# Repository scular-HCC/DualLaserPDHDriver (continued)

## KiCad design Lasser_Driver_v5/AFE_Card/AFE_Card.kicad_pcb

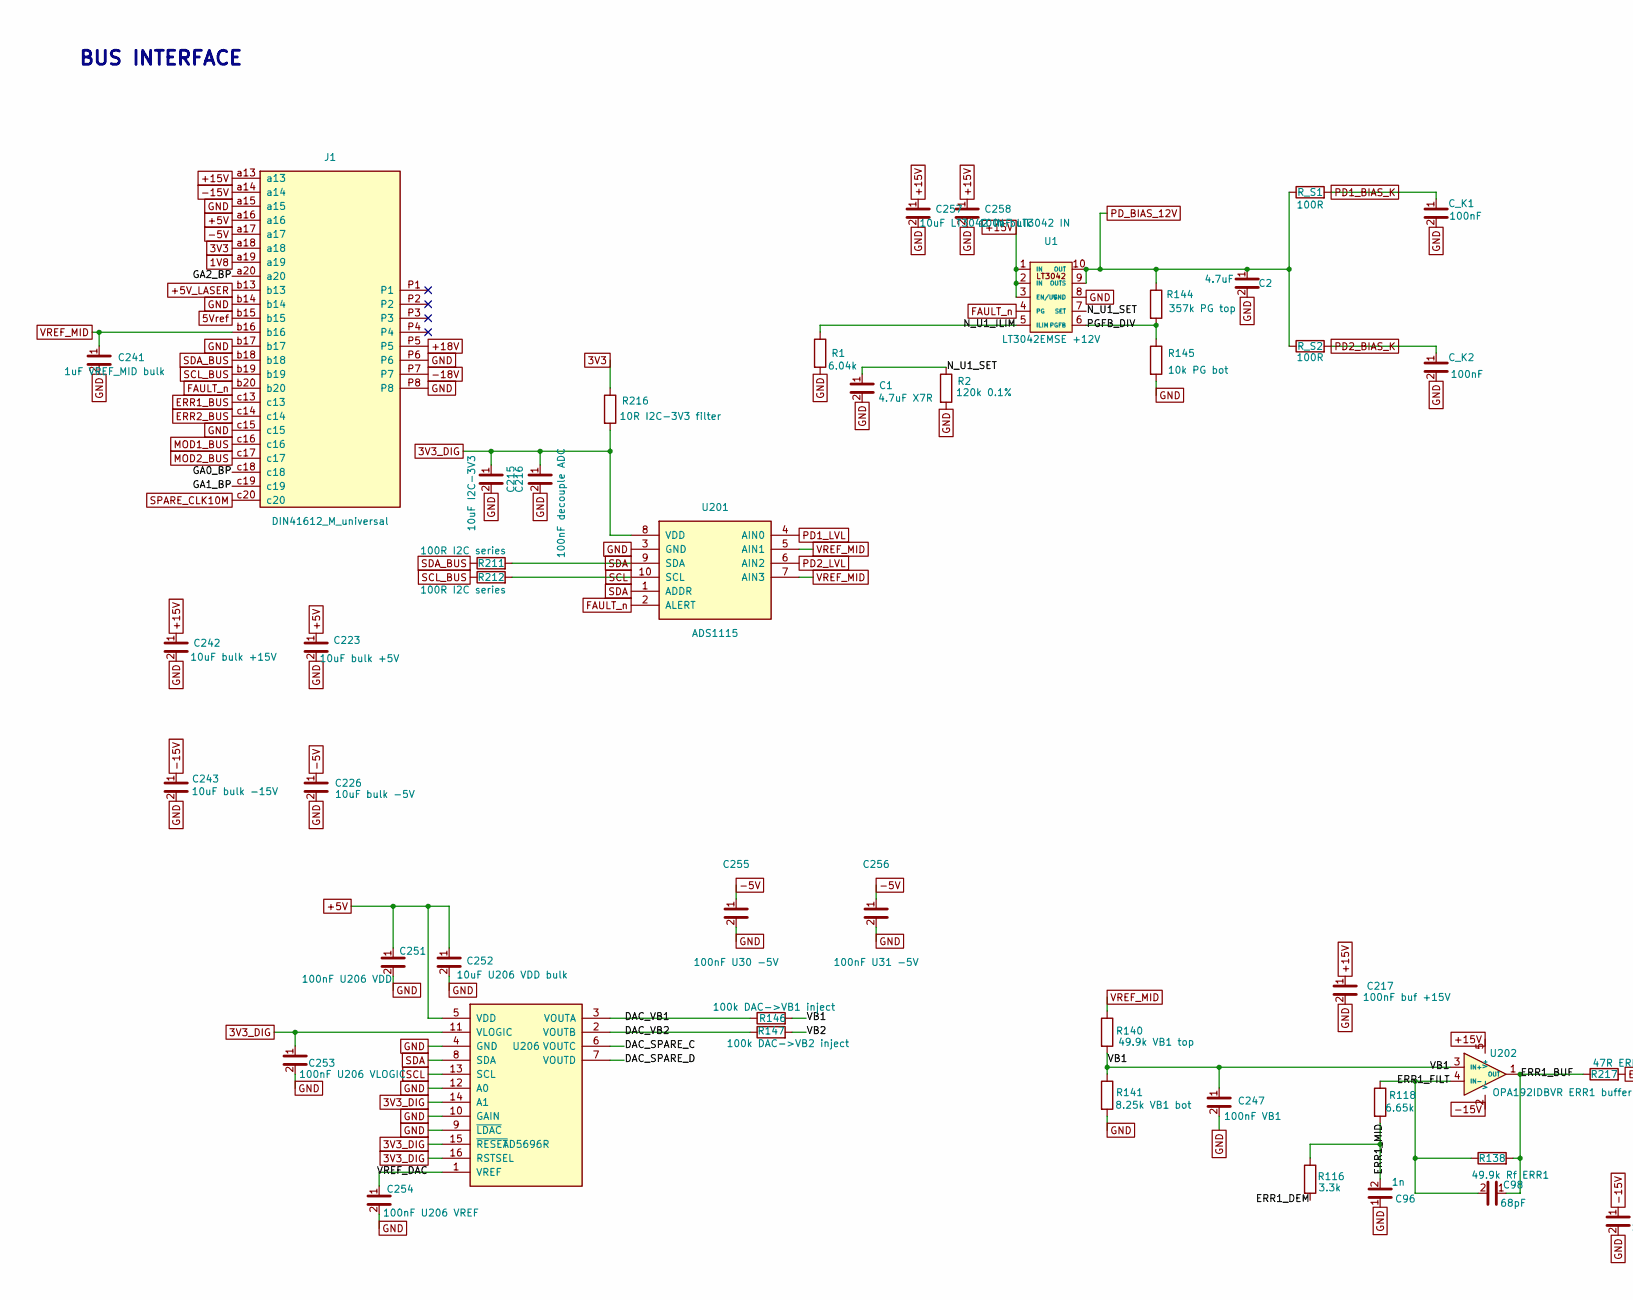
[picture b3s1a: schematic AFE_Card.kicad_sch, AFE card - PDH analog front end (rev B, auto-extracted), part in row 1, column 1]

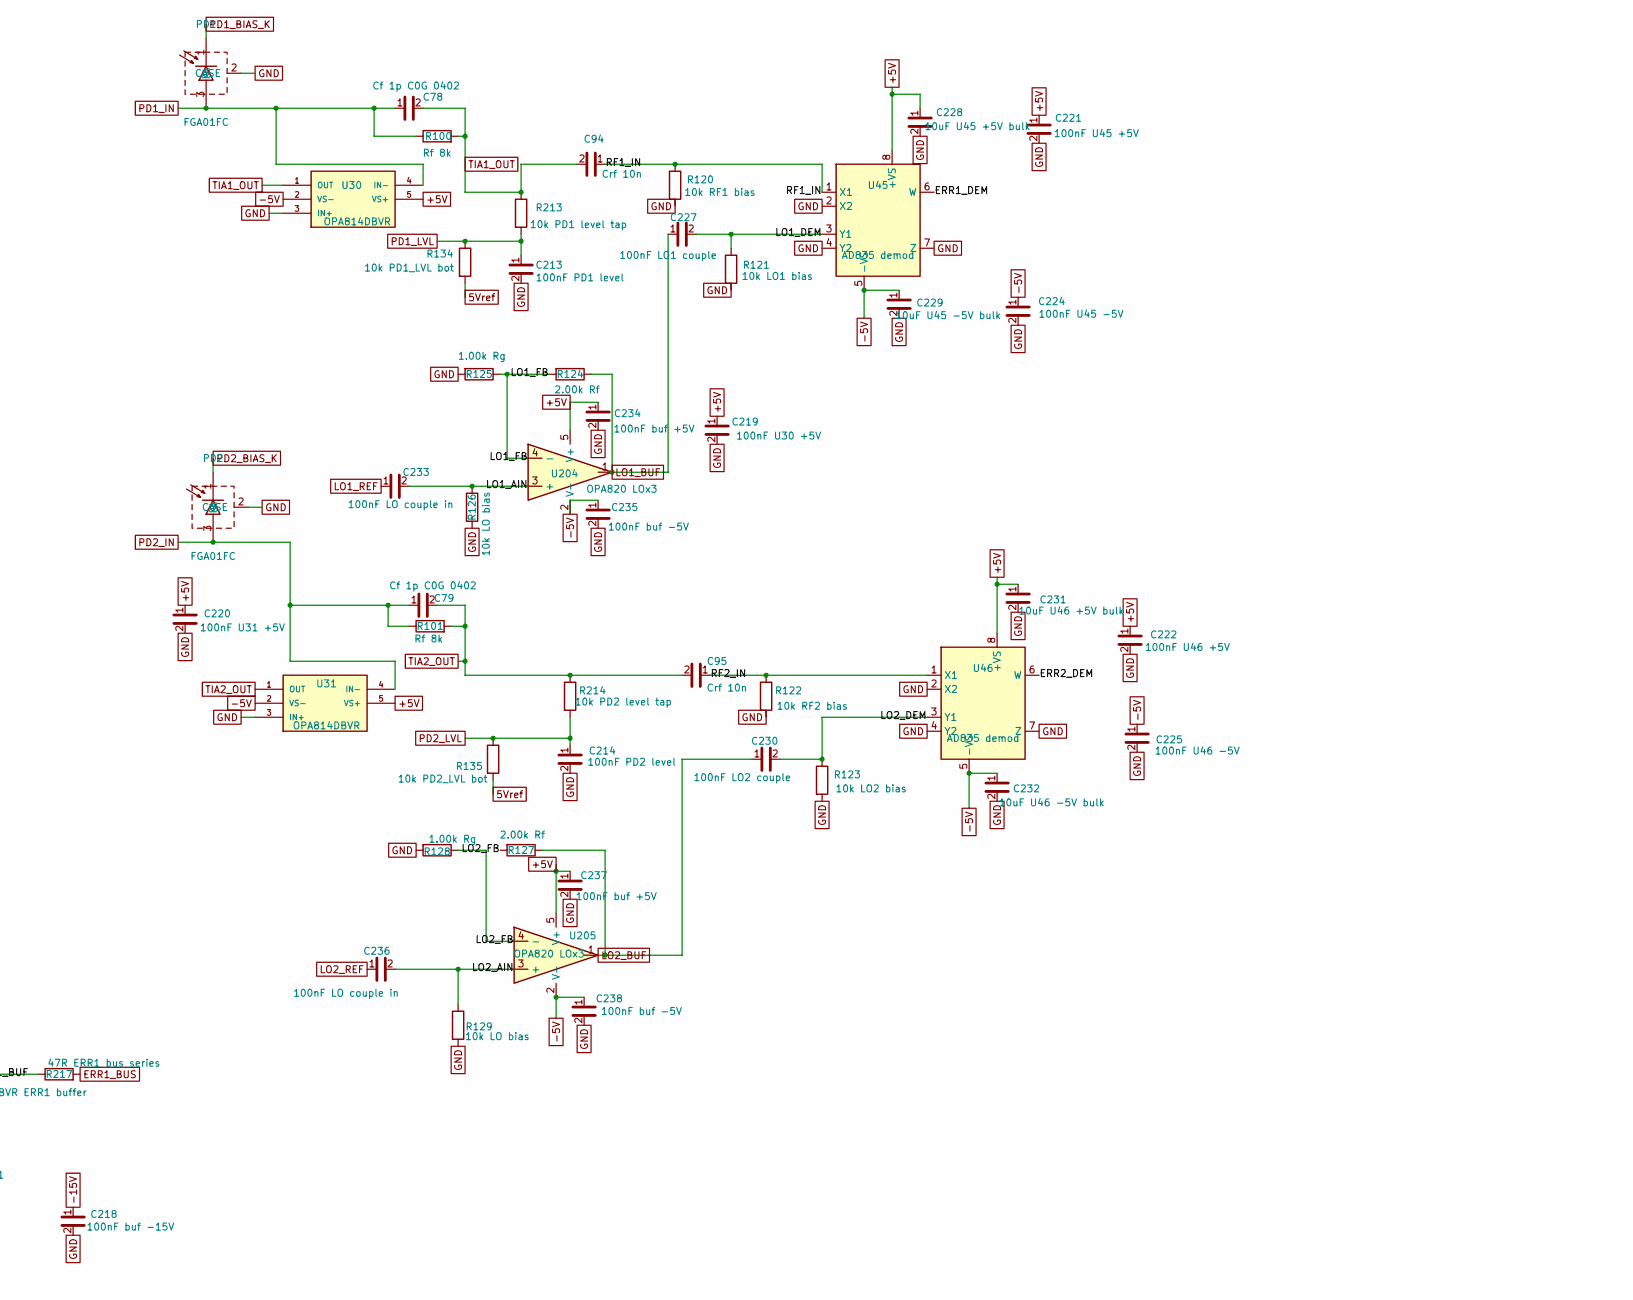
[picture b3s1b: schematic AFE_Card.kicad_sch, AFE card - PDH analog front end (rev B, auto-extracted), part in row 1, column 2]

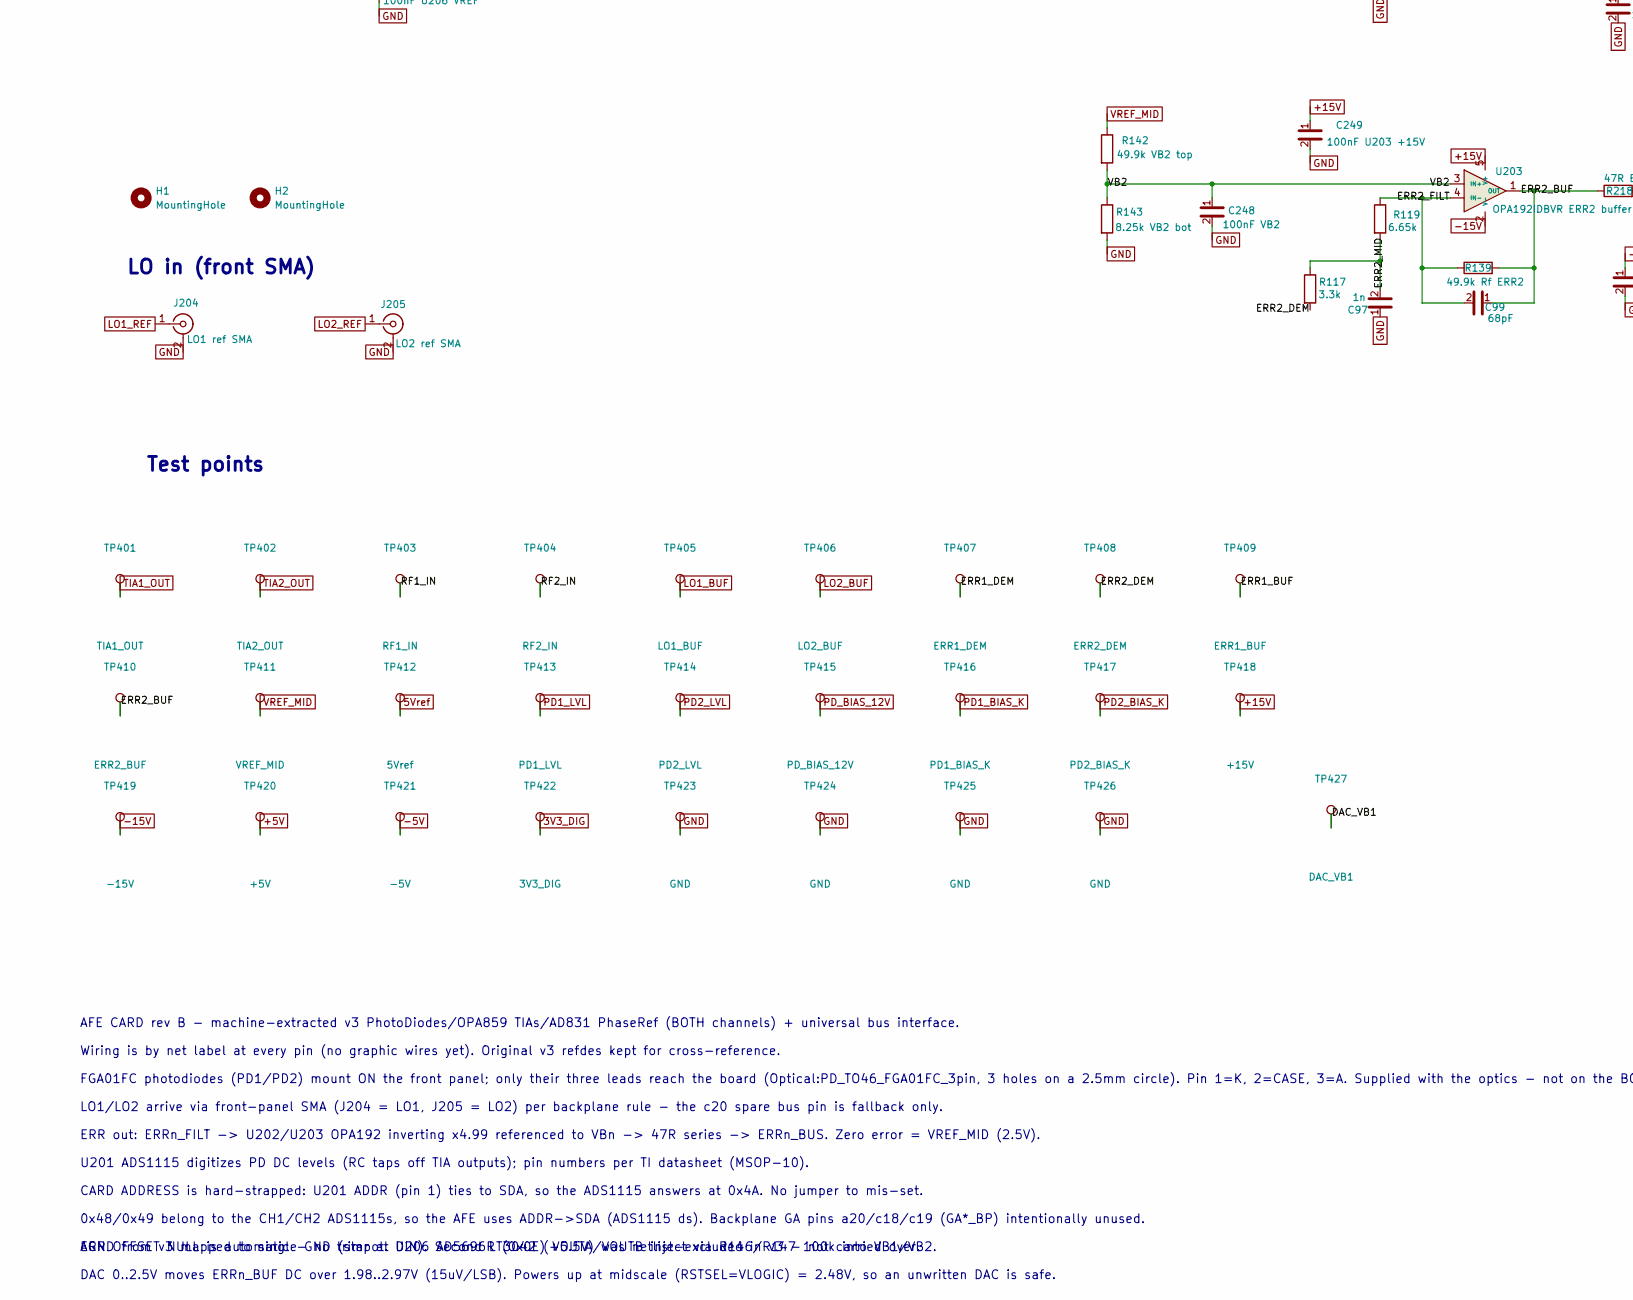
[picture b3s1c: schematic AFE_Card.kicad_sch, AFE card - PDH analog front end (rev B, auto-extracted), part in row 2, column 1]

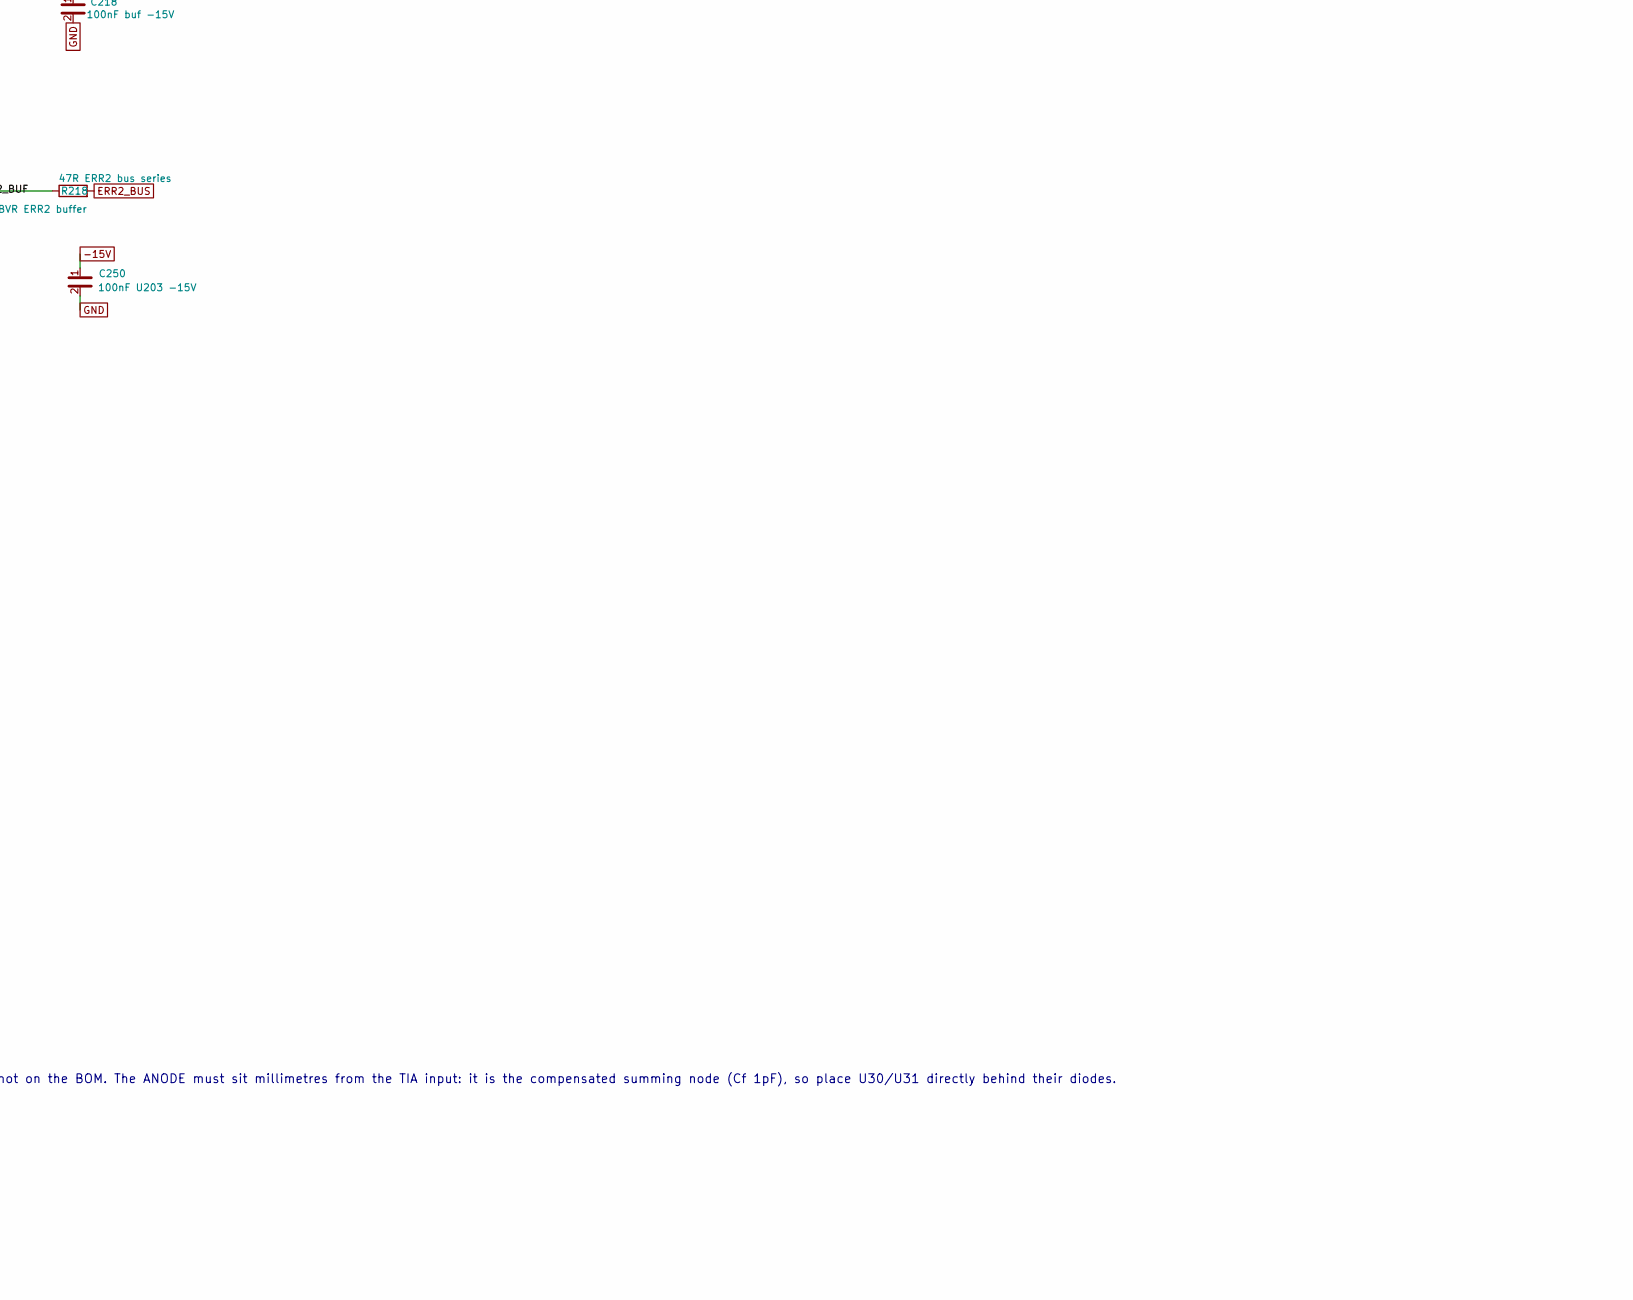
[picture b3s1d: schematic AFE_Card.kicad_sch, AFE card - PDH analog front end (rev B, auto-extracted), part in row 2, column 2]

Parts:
C1: 4.7uF X7R; C_0805_2012Metric_Pad1.18x1.45mm_HandSolder
C2: 4.7uF; C_0805_2012Metric_Pad1.18x1.45mm_HandSolder
C78, C79: Cf 1p C0G 0402; C_0402_1005Metric_Pad0.74x0.62mm_HandSolder
C94, C95: Crf 10n; C_0805_2012Metric_Pad1.18x1.45mm_HandSolder
C96, C97: 1n; C_0805_2012Metric_Pad1.18x1.45mm_HandSolder
C98, C99: 68pF; C_0805_2012Metric_Pad1.18x1.45mm_HandSolder
C213: 100nF PD1 level; C_0805_2012Metric_Pad1.18x1.45mm_HandSolder
C214: 100nF PD2 level; C_0805_2012Metric_Pad1.18x1.45mm_HandSolder
C215: 10uF I2C-3V3; C_0805_2012Metric_Pad1.18x1.45mm_HandSolder
C216: 100nF decouple ADC; C_0805_2012Metric_Pad1.18x1.45mm_HandSolder
C217: 100nF buf +15V; C_0805_2012Metric_Pad1.18x1.45mm_HandSolder
C218: 100nF buf -15V; C_0805_2012Metric_Pad1.18x1.45mm_HandSolder
C219: 100nF U30 +5V; C_0805_2012Metric_Pad1.18x1.45mm_HandSolder
C220: 100nF U31 +5V; C_0805_2012Metric_Pad1.18x1.45mm_HandSolder
C221: 100nF U45 +5V; C_0805_2012Metric_Pad1.18x1.45mm_HandSolder
C222: 100nF U46 +5V; C_0805_2012Metric_Pad1.18x1.45mm_HandSolder
C223: 10uF bulk +5V; C_0805_2012Metric_Pad1.18x1.45mm_HandSolder
C224: 100nF U45 -5V; C_0805_2012Metric_Pad1.18x1.45mm_HandSolder
C225: 100nF U46 -5V; C_0805_2012Metric_Pad1.18x1.45mm_HandSolder
C226: 10uF bulk -5V; C_0805_2012Metric_Pad1.18x1.45mm_HandSolder
C227: 100nF LO1 couple; C_0805_2012Metric_Pad1.18x1.45mm_HandSolder
C228: 10uF U45 +5V bulk; C_0805_2012Metric_Pad1.18x1.45mm_HandSolder
C229: 10uF U45 -5V bulk; C_0805_2012Metric_Pad1.18x1.45mm_HandSolder
C230: 100nF LO2 couple; C_0805_2012Metric_Pad1.18x1.45mm_HandSolder
C231: 10uF U46 +5V bulk; C_0805_2012Metric_Pad1.18x1.45mm_HandSolder
C232: 10uF U46 -5V bulk; C_0805_2012Metric_Pad1.18x1.45mm_HandSolder
C233, C236: 100nF LO couple in; C_0805_2012Metric_Pad1.18x1.45mm_HandSolder
C234, C237: 100nF buf +5V; C_0805_2012Metric_Pad1.18x1.45mm_HandSolder
C235, C238: 100nF buf -5V; C_0805_2012Metric_Pad1.18x1.45mm_HandSolder
C241: 1uF VREF_MID bulk; C_0805_2012Metric_Pad1.18x1.45mm_HandSolder
C242: 10uF bulk +15V; C_0805_2012Metric_Pad1.18x1.45mm_HandSolder
C243: 10uF bulk -15V; C_0805_2012Metric_Pad1.18x1.45mm_HandSolder
C247: 100nF VB1; C_0805_2012Metric_Pad1.18x1.45mm_HandSolder
C248: 100nF VB2; C_0805_2012Metric_Pad1.18x1.45mm_HandSolder
C249: 100nF U203 +15V; C_0805_2012Metric_Pad1.18x1.45mm_HandSolder
C250: 100nF U203 -15V; C_0805_2012Metric_Pad1.18x1.45mm_HandSolder
C251: 100nF U206 VDD; C_0805_2012Metric_Pad1.18x1.45mm_HandSolder
C252: 10uF U206 VDD bulk; C_0805_2012Metric_Pad1.18x1.45mm_HandSolder
C253: 100nF U206 VLOGIC; C_0805_2012Metric_Pad1.18x1.45mm_HandSolder
C254: 100nF U206 VREF; C_0805_2012Metric_Pad1.18x1.45mm_HandSolder
C255: 100nF U30 -5V; C_0805_2012Metric_Pad1.18x1.45mm_HandSolder
C256: 100nF U31 -5V; C_0805_2012Metric_Pad1.18x1.45mm_HandSolder
C257: 10uF LT3042 IN bulk; C_0805_2012Metric_Pad1.18x1.45mm_HandSolder
C258: 100nF LT3042 IN; C_0805_2012Metric_Pad1.18x1.45mm_HandSolder
C_K1, C_K2: 100nF; C_0805_2012Metric_Pad1.18x1.45mm_HandSolder
H1, H2: MountingHole; MountingHole_2.7mm
J1: DIN41612_M_universal; DIN41612_M_3x8+8_Male_Horizontal_THT_Power
J204: LO1 ref SMA; SMA_Amphenol_132203-12_Horizontal
J205: LO2 ref SMA; SMA_Amphenol_132203-12_Horizontal
PD1, PD2: FGA01FC; PD_FGA01FC_EdgeBracket
R1: 6.04k; R_0805_2012Metric_Pad1.20x1.40mm_HandSolder
R2: 120k 0.1%; R_0805_2012Metric_Pad1.20x1.40mm_HandSolder
R100, R101: Rf 8k; R_0805_2012Metric_Pad1.20x1.40mm_HandSolder
R116, R117: 3.3k; R_0805_2012Metric_Pad1.20x1.40mm_HandSolder
R118, R119: 6.65k; R_0805_2012Metric_Pad1.20x1.40mm_HandSolder
R120: 10k RF1 bias; R_0805_2012Metric_Pad1.20x1.40mm_HandSolder
R121: 10k LO1 bias; R_0805_2012Metric_Pad1.20x1.40mm_HandSolder
R122: 10k RF2 bias; R_0805_2012Metric_Pad1.20x1.40mm_HandSolder
R123: 10k LO2 bias; R_0805_2012Metric_Pad1.20x1.40mm_HandSolder
R124, R127: 2.00k Rf; R_0805_2012Metric_Pad1.20x1.40mm_HandSolder
R125, R128: 1.00k Rg; R_0805_2012Metric_Pad1.20x1.40mm_HandSolder
R126, R129: 10k LO bias; R_0805_2012Metric_Pad1.20x1.40mm_HandSolder
R134: 10k PD1_LVL bot; R_0805_2012Metric_Pad1.20x1.40mm_HandSolder
R135: 10k PD2_LVL bot; R_0805_2012Metric_Pad1.20x1.40mm_HandSolder
R138: 49.9k Rf ERR1; R_0805_2012Metric_Pad1.20x1.40mm_HandSolder
R139: 49.9k Rf ERR2; R_0805_2012Metric_Pad1.20x1.40mm_HandSolder
R140: 49.9k VB1 top; R_0805_2012Metric_Pad1.20x1.40mm_HandSolder
R141: 8.25k VB1 bot; R_0805_2012Metric_Pad1.20x1.40mm_HandSolder
R142: 49.9k VB2 top; R_0805_2012Metric_Pad1.20x1.40mm_HandSolder
R143: 8.25k VB2 bot; R_0805_2012Metric_Pad1.20x1.40mm_HandSolder
R144: 357k PG top; R_0805_2012Metric_Pad1.20x1.40mm_HandSolder
R145: 10k PG bot; R_0805_2012Metric_Pad1.20x1.40mm_HandSolder
R146: 100k DAC->VB1 inject; R_0805_2012Metric_Pad1.20x1.40mm_HandSolder
R147: 100k DAC->VB2 inject; R_0805_2012Metric_Pad1.20x1.40mm_HandSolder
R211, R212: 100R I2C series; R_0805_2012Metric_Pad1.20x1.40mm_HandSolder
R213: 10k PD1 level tap; R_0805_2012Metric_Pad1.20x1.40mm_HandSolder
R214: 10k PD2 level tap; R_0805_2012Metric_Pad1.20x1.40mm_HandSolder
R216: 10R I2C-3V3 filter; R_0805_2012Metric_Pad1.20x1.40mm_HandSolder
R217: 47R ERR1 bus series; R_0805_2012Metric_Pad1.20x1.40mm_HandSolder
R218: 47R ERR2 bus series; R_0805_2012Metric_Pad1.20x1.40mm_HandSolder
R_S1, R_S2: 100R; R_0805_2012Metric_Pad1.20x1.40mm_HandSolder
TP401: TIA1_OUT; TestPoint_Pad_D1.0mm
TP402: TIA2_OUT; TestPoint_Pad_D1.0mm
TP403: RF1_IN; TestPoint_Pad_D1.0mm
TP404: RF2_IN; TestPoint_Pad_D1.0mm
TP405: LO1_BUF; TestPoint_Pad_D1.0mm
TP406: LO2_BUF; TestPoint_Pad_D1.0mm
TP407: ERR1_DEM; TestPoint_Pad_D1.0mm
TP408: ERR2_DEM; TestPoint_Pad_D1.0mm
TP409: ERR1_BUF; TestPoint_Pad_D1.0mm
TP410: ERR2_BUF; TestPoint_Pad_D1.0mm
TP411: VREF_MID; TestPoint_Pad_D1.0mm
TP412: 5Vref; TestPoint_Pad_D1.0mm
TP413: PD1_LVL; TestPoint_Pad_D1.0mm
TP414: PD2_LVL; TestPoint_Pad_D1.0mm
TP415: PD_BIAS_12V; TestPoint_Pad_D1.0mm
TP416: PD1_BIAS_K; TestPoint_Pad_D1.0mm
TP417: PD2_BIAS_K; TestPoint_Pad_D1.0mm
TP418: +15V; TestPoint_Pad_D1.0mm
TP419: -15V; TestPoint_Pad_D1.0mm
TP420: +5V; TestPoint_Pad_D1.0mm
TP421: -5V; TestPoint_Pad_D1.0mm
TP422: 3V3_DIG; TestPoint_Pad_D1.0mm
TP423, TP424, TP425, TP426: GND; TestPoint_THTPad_D1.5mm_Drill0.7mm
TP427: DAC_VB1; TestPoint_Pad_D1.0mm
U1: LT3042EMSE +12V; MSOP-10-1EP_3x3mm_P0.5mm_EP2.2x3.1mm_Mask1.83x1.89mm_Therma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
U30, U31: OPA814DBVR; MOUSER_PART_NUMBER 595-OPA814DBVR
U45, U46: AD835 demod; SOIC-8_3.9x4.9mm_P1.27mm
U201: ADS1115; MSOP-10_3x3mm_P0.5mm
U202: OPA192IDBVR ERR1 buffer; SOT-23-5
U203: OPA192IDBVR ERR2 buffer; SOT-23-5
U204, U205: OPA820 LOx3; SOT-23-5
U206: AD5696R; TSSOP-16_4.4x5mm_P0.65mm

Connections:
1V8: J1.a19
3V3: J1.a18, R216.1
3V3_DIG: C215.1, C216.1, C253.1, R216.2, TP422.1 (1_1), U201.8 (VDD), U206.11 (VLOGIC), U206.14 (A1), U206.15 (~RESET), U206.16 (RSTSEL)
5Vref: J1.b15, R134.2, R135.2, TP412.1 (1_1)
+5V: C219.1, C220.1, C221.1, C222.1, C223.1, C228.1, C231.1, C234.1, C237.1, C251.1, C252.1, J1.a16, TP420.1 (1_1), U30.5 (VS+), U31.5 (VS+), U45.8 (+VS), U46.8 (+VS), U204.5 (V+), U205.5 (V+), U206.5 (VDD)
+5V_LASER: J1.b13
+15V: C217.1, C242.1, C249.1, C257.1, C258.1, J1.a13, TP418.1 (1_1), U1.1 (IN), U1.2 (IN), U1.3 (EN/UV), U202.5 (V+), U203.5 (V+)
+18V: J1.P5
-5V: C224.1, C225.1, C226.1, C229.1, C232.1, C235.1, C238.1, C255.1, C256.1, J1.a17, TP421.1 (1_1), U30.2 (VS-), U31.2 (VS-), U45.5 (-VS), U46.5 (-VS), U204.2 (V-), U205.2 (V-)
-15V: C218.1, C243.1, C250.1, J1.a14, TP419.1 (1_1), U202.2 (V-), U203.2 (V-)
-18V: J1.P7
/DAC_SPARE_C: U206.6 (VOUTC)
/DAC_SPARE_D: U206.7 (VOUTD)
/DAC_VB1: R146.1, TP427.1 (1_1), U206.3 (VOUTA)
/DAC_VB2: R147.1, U206.2 (VOUTB)
/ERR1_BUF: C98.1, R138.2, R217.1, TP409.1 (1_1), U202.1 (OUT)
/ERR1_DEM: R116.2, TP407.1 (1_1), U45.6 (W)
/ERR1_FILT: C98.2, R118.1, R138.1, U202.4 (IN-)
/ERR1_MID: C96.2, R116.1, R118.2
/ERR2_BUF: C99.1, R139.2, R218.1, TP410.1 (1_1), U203.1 (OUT)
/ERR2_DEM: R117.2, TP408.1 (1_1), U46.6 (W)
/ERR2_FILT: C99.2, R119.1, R139.1, U203.4 (IN-)
/ERR2_MID: C97.2, R117.1, R119.2
/GA0_BP: J1.c18
/GA1_BP: J1.c19
/GA2_BP: J1.a20
/LO1_AIN: C233.2, R126.1, U204.3 (+)
/LO1_DEM: C227.2, R121.1, U45.3 (Y1)
/LO1_FB: R124.2, R125.1, U204.4 (-)
/LO2_AIN: C236.2, R129.1, U205.3 (+)
/LO2_DEM: C230.2, R123.1, U46.3 (Y1)
/LO2_FB: R127.2, R128.1, U205.4 (-)
/N_U1_ILIM: R1.1, U1.5 (ILIM)
/N_U1_SET: C1.1, R2.1, U1.7 (SET)
/PGFB_DIV: R144.2, R145.1, U1.6 (PGFB)
/RF1_IN: C94.1, R120.1, TP403.1 (1_1), U45.1 (X1)
/RF2_IN: C95.1, R122.1, TP404.1 (1_1), U46.1 (X1)
/VB1: C247.1, R140.2, R141.1, R146.2, U202.3 (IN+)
/VB2: C248.1, R142.2, R143.1, R147.2, U203.3 (IN+)
/VREF_DAC: C254.1, U206.1 (VREF)
ERR1_BUS: J1.c13, R217.2
ERR2_BUS: J1.c14, R218.2
FAULT_n: J1.b20, U1.4 (PG), U201.2 (ALERT)
GND: C1.2, C2.2, C96.1, C97.1, C213.2, C214.2, C215.2, C216.2, C217.2, C218.2, C219.2, C220.2, C221.2, C222.2, C223.2, C224.2, C225.2, C226.2, C228.2, C229.2, C231.2, C232.2, C234.2, C235.2, C237.2, C238.2, C241.2, C242.2, C243.2, C247.2, C248.2, C249.2, C250.2, C251.2, C252.2, C253.2, C254.2, C255.2, C256.2, C257.2, C258.2, C_K1.2, C_K2.2, J1.P6, J1.P8, J1.a15, J1.b14, J1.b17, J1.c15, J204.2 (Ext), J205.2 (Ext), PD1.2 (CASE), PD2.2 (CASE), R1.2, R2.2, R120.2, R121.2, R122.2, R123.2, R125.2, R126.2, R128.2, R129.2, R141.2, R143.2, R145.2, TP423.1 (1_1), TP424.1 (1_1), TP425.1 (1_1), TP426.1 (1_1), U1.8 (GND), U1.11 (Pad), U30.3 (IN+), U31.3 (IN+), U45.2 (X2), U45.4 (Y2), U45.7 (Z), U46.2 (X2), U46.4 (Y2), U46.7 (Z), U201.3 (GND), U206.4 (GND), U206.9 (~LDAC), U206.10 (GAIN), U206.12 (A0)
LO1_BUF: C227.1, R124.1, TP405.1 (1_1), U204.1
LO1_REF: C233.1, J204.1 (In)
LO2_BUF: C230.1, R127.1, TP406.1 (1_1), U205.1
LO2_REF: C236.1, J205.1 (In)
MOD1_BUS: J1.c16
MOD2_BUS: J1.c17
PD1_BIAS_K: C_K1.1, PD1.1 (K), R_S1.2, TP416.1 (1_1)
PD1_IN: C78.1, PD1.3 (A), R100.1, U30.4 (IN-)
PD1_LVL: C213.1, R134.1, R213.2, TP413.1 (1_1), U201.4 (AIN0)
PD2_BIAS_K: C_K2.1, PD2.1 (K), R_S2.2, TP417.1 (1_1)
PD2_IN: C79.1, PD2.3 (A), R101.1, U31.4 (IN-)
PD2_LVL: C214.1, R135.1, R214.2, TP414.1 (1_1), U201.6 (AIN2)
PD_BIAS_12V: C2.1, R144.1, R_S1.1, R_S2.1, TP415.1 (1_1), U1.9 (OUTS), U1.10 (OUT)
SCL: R212.2, U201.10 (SCL), U206.13 (SCL)
SCL_BUS: J1.b19, R212.1
SDA: R211.2, U201.1 (ADDR), U201.9 (SDA), U206.8 (SDA)
SDA_BUS: J1.b18, R211.1
SPARE_CLK10M: J1.c20
TIA1_OUT: C78.2, C94.2, R100.2, R213.1, TP401.1 (1_1), U30.1 (OUT)
TIA2_OUT: C79.2, C95.2, R101.2, R214.1, TP402.1 (1_1), U31.1 (OUT)
VREF_MID: C241.1, J1.b16, R140.1, R142.1, TP411.1 (1_1), U201.5 (AIN1), U201.7 (AIN3)

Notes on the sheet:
AFE CARD rev B - machine-extracted v3 PhotoDiodes/OPA859 TIAs/AD831 PhaseRef (BOTH channels) + universal bus interface.
U201 ADS1115 digitizes PD DC levels (RC taps off TIA outputs); pin numbers per TI datasheet (MSOP-10).
LO in (front SMA)
CARD ADDRESS is hard-strapped: U201 ADDR (pin 1) ties to SDA, so the ADS1115 answers at 0x4A. No jumper to mis-set.
LO1/LO2 arrive via front-panel SMA (J204 = LO1, J205 = LO2) per backplane rule - the c20 spare bus pin is fallback only.
Test points
BUS INTERFACE
Wiring is by net label at every pin (no graphic wires yet). Original v3 refdes kept for cross-reference.
DAC 0..2.5V moves ERRn_BUF DC over 1.98..2.97V (15uV/LSB). Powers up at midscale (RSTSEL=VLOGIC) = 2.48V, so an unwritten DAC is safe.
AGND from v3 mapped to single GND (star at DIN). Second LT3042 (+5.5V) was netlist-excluded in v3 - not carried over.
FGA01FC photodiodes (PD1/PD2) mount ON the front panel; only their three leads reach the board (Optical:PD_TO46_FGA01FC_3pin, 3 holes on a 2.5mm circle). Pin 1=K, 2=CASE, 3=A. Supplied with the optics - not on the BOM. The ANODE must sit millimetres from the TIA input: it is the compensated summing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
ERR out: ERRn_FILT -> U202/U203 OPA192 inverting x4.99 referenced to VBn -> 47R series -> ERRn_BUS. Zero error = VREF_MID (2.5V).
ERR OFFSET NULL is automatic - no trimpot. U206 AD5696R (0x0E) VOUTA/VOUTB inject via R146/R147 100k into VB1/VB2.
0x48/0x49 belong to the CH1/CH2 ADS1115s, so the AFE uses ADDR->SDA (ADS1115 ds). Backplane GA pins a20/c18/c19 (GA*_BP) intentionally unused.

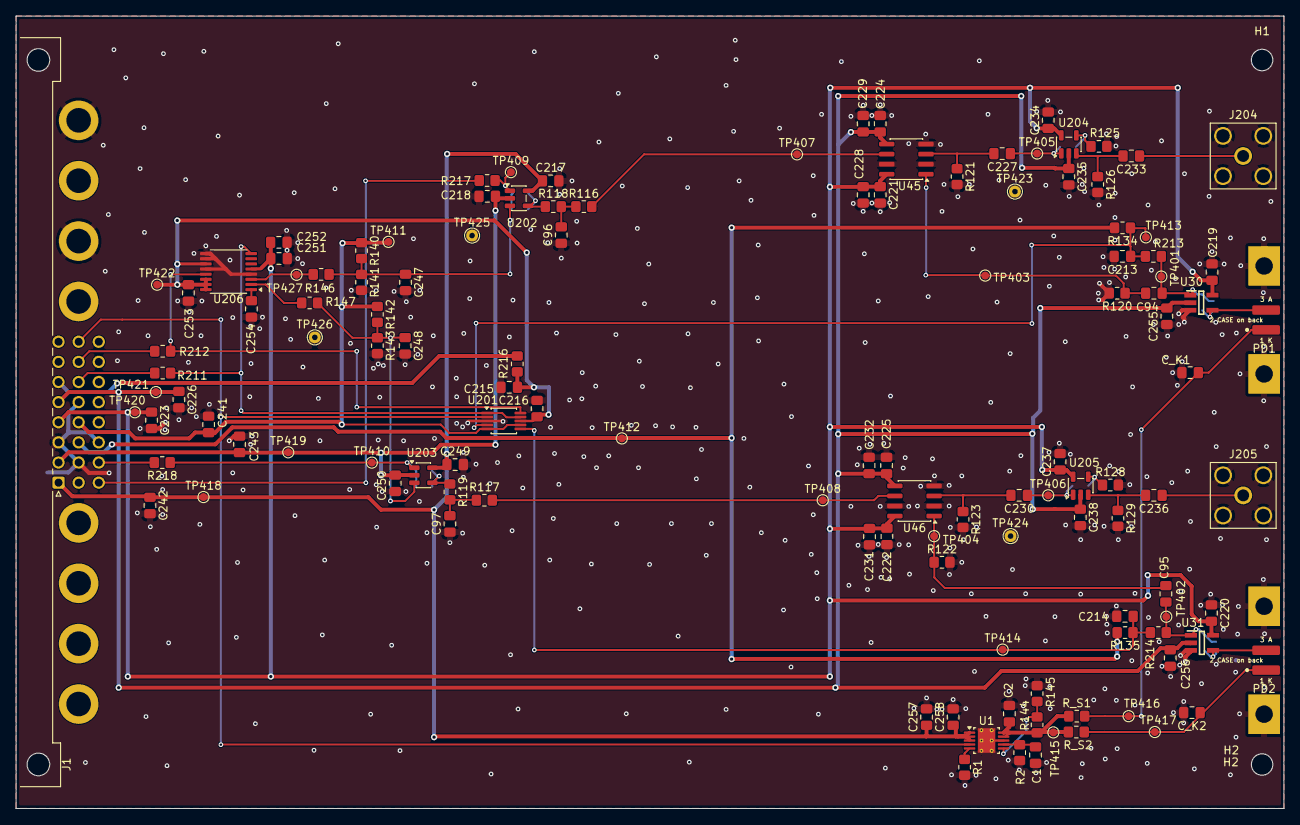
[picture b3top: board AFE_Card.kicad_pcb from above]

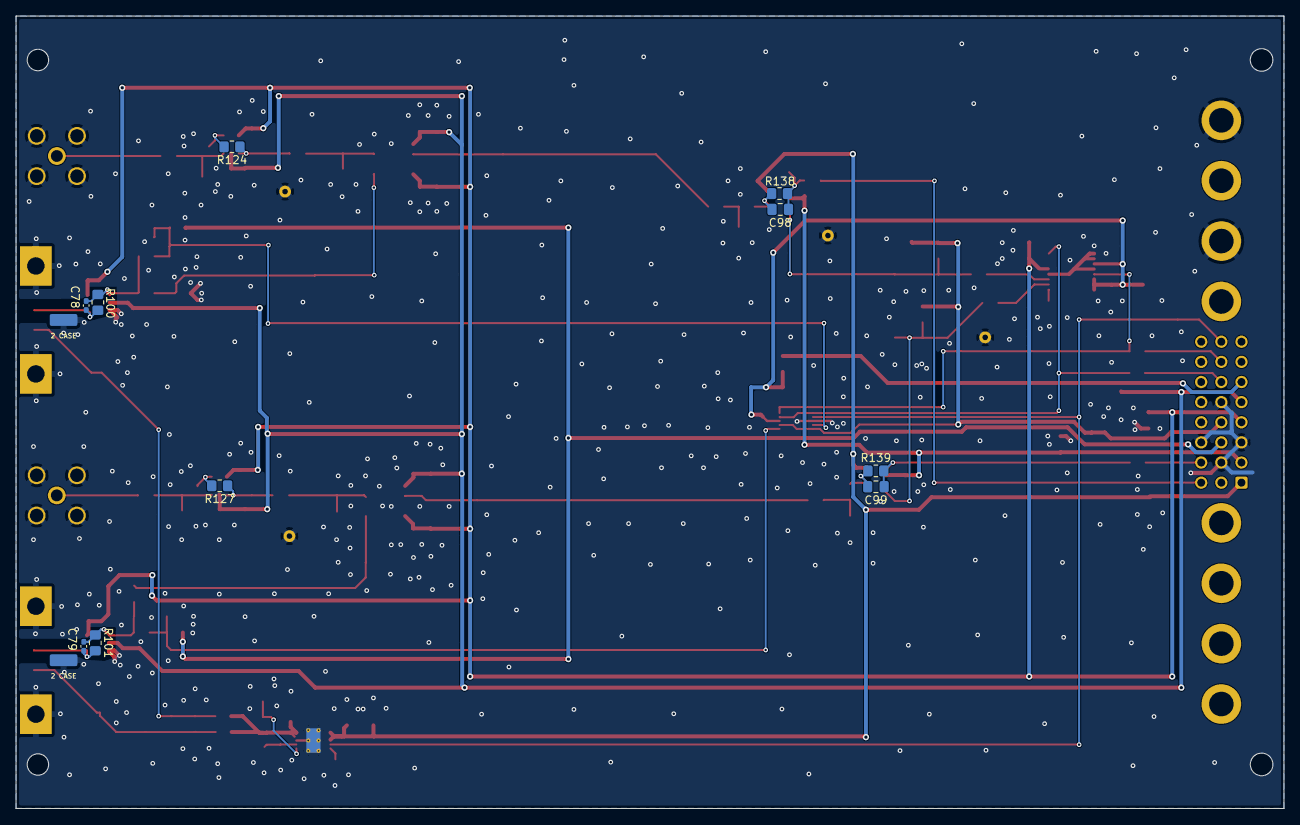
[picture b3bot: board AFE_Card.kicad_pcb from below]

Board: 2 copper layers, 160.0 x 100.0 mm, 137 parts (10 on the bottom side), 53 nets.

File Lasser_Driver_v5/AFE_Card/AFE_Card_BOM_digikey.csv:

Quantity,Manufacturer Part Number,Manufacturer,Customer Reference,Value,Footprint,Description
2,132203,Amphenol RF,"AFE_Card J204,J205",SMA jack R/A,SMA_Amphenol_132203-12_Horizontal,"SMA PCB right-angle jack 50ohm, LO1/LO2 ref input (J204/J205 - now two discrete jacks)"
1,374144-E,TE Connectivity,AFE_Card J1,DIN41612 M 3x8+8,DIN41612_M_3x8+8,DIN41612 Type M 24sig+8pwr R/A male backplane conn (J1)
1,AD5696RARUZ,Analog Devices,AFE_Card U206,AD5696R,TSSOP-16,"Quad 16-bit I2C DAC at 0x0E (A1=VLOGIC,A0=GND), int 2.5V ref, GAIN=GND -> 0..2.5V; automatic ERR offset null via R146/R147 (U206)"
2,AD835ARZ,Analog Devices,"AFE_Card U45,U46",AD835,SOIC-8,"250MHz 4-quadrant multiplier, PDH demodulator (U45/46)"
1,ADS1115IDGSR,Texas Instruments,AFE_Card U201,ADS1115,VSSOP-10,"16-bit 4ch I2C ADC at 0x4A (ADDR->SDA), differential PD level monitor (U201)"
1,C0805C105K5RACTU,Kemet,AFE_Card C241,1uF,C_0805,MLCC 1uF 50V X7R 0805 (VREF_MID local bulk)
10,C0805C106K3PACTU,Kemet,"AFE_Card C215,C223,C226,C228,C229,C231,C232,C242,C243,C252",10uF,C_0805,"MLCC 10uF 25V X5R 0805 (rail bulk +/-5V, +/-15V, I2C-3V3, VREF_TIA)"
2,C0805C475K3RACTU,Kemet,"AFE_Card C1,C2",4.7uF,C_0805,MLCC 4.7uF 25V X7R 0805 (LT3042 SET soft-start + output)
2,C0805C680J5GACTU,Kemet,"AFE_Card C98,C99",68pF C0G,C_0805,"MLCC 68pF 50V C0G 0805 (ERR stage 2nd pole, across Rf C98/99)"
2,CL21B102KBANNNC,Samsung,"AFE_Card C96,C97",1nF,C_0805,MLCC 1nF 50V X7R 0805 (ERR filter 1st pole C96/97)
2,CL21B103KBANNNC,Samsung,"AFE_Card C94,C95",10nF,C_0805,MLCC 10nF 50V X7R 0805 (TIA->mixer RF AC-couple C94/95)
30,CL21B104KBCNNNC,Samsung,"AFE_Card C213,C214,C216,C217,C218,C219,C220,C221,C222,C224,C225,C227,C230,C233,C234,C235,C236,C237,C238,C247,C248,C249,C250,C251,C253,C254,C255,C256,C_K1,C_K2",100nF,C_0805,MLCC 100nF 50V X7R 0805 (decoupling + coupling + PD level + VB bypass)
2,CRCW08051K00FKEA,Vishay Dale,"AFE_Card R125,R128",1.00k,R_0805,Res 1.00k 1% 0805 (LO buffer Rg; Av=1+Rf/Rg=3)
1,ERA-6AEB124V,Panasonic,AFE_Card R2,120k 0.1%,R_0805,Res 120k 0.1% 0805 (LT3042 SET -> 12V PD bias)
1,ERJ-6ENF3573V,Panasonic,AFE_Card R144,357k,R_0805,Res 357k 1% 0805 (LT3042 PGFB divider top; PG trips at 11.0V)
2,GRM1555C1H1R0CA01D,Murata,"AFE_Card C78,C79",1pF C0G,C_0402,MLCC 1.0pF 50V C0G 0402 (TIA feedback Cf C78/79)
1,LT3042EMSE#PBF,Analog Devices,AFE_Card U1,LT3042,MSOP-10-EP,"Ultralow-noise LDO, SET=120k->12V PD bias (U1)"
2,OPA192IDBVR,Texas Instruments,"AFE_Card U202,U203",OPA192,SOT-23-5,"Precision op-amp, ERR inverting x5.02 level-shift output stage (U202/203)"
2,OPA814DBVR,Texas Instruments,"AFE_Card U30,U31",OPA814,SOT-23-5,"250MHz GBW JFET-input op-amp, PD transimpedance TIA (U30/31). Ground-referenced on +/-5V: the +/-5V CM ceiling is +2.1V so the old 3.336V VREF_TIA was out of range"
2,OPA820IDBVR,Texas Instruments,"AFE_Card U204,U205",OPA820,SOT-23-5,"240MHz VFB op-amp, LO x3 buffer +/-5V (U204/205)"
2,RC0805FR-07100KL,Yageo,"AFE_Card R146,R147",100k,R_0805,Res 100k 1% 0805 (VREF_TIA bottom leg -> 3.336V TIA reference)
4,RC0805FR-07100RL,Yageo,"AFE_Card R211,R212,R_S1,R_S2",100R,R_0805,Res 100R 1% 0805 (I2C series R211/212; VREF_TIA RC R130/131; PD bias R_S1/2)
11,RC0805FR-0710KL,Yageo,"AFE_Card R120,R121,R122,R123,R126,R129,R134,R135,R145,R213,R214",10k,R_0805,"Res 10k 1% 0805 (AD835 X/Y bias, LO bias, ADC dividers, PG bot)"
1,RC0805FR-0710RL,Yageo,AFE_Card R216,10R,R_0805,Res 10R 1% 0805 (I2C-3V3 filter R216)
2,RC0805FR-072KL,Yageo,"AFE_Card R124,R127",2.00k,R_0805,"Res 2.00k 1% 0805 (LO buffer Rf, gain set)"
2,RC0805FR-073K3L,Yageo,"AFE_Card R116,R117",3.3k,R_0805,Res 3.3k 1% 0805 (ERR filter 1st pole R116/117; also the upper half of the ERR stage Ri = 3.3k+6.65k = 9.95k)
2,RC0805FR-0747RL,Yageo,"AFE_Card R217,R218",47R,R_0805,Res 47R 1% 0805 (ERR bus series R217/218)
4,RC0805FR-0749K9L,Yageo,"AFE_Card R138,R139,R140,R142",49.9k,R_0805,Res 49.9k 1% 0805 (ERR stage Rf R138/139 -> Av=-5.02 into Ri=9.95k; VB dividers)
1,RC0805FR-076K04L,Yageo,AFE_Card R1,6.04k,R_0805,Res 6.04k 1% 0805 (LT3042 ILIM ~21mA)
2,RC0805FR-076K65L,Yageo,"AFE_Card R118,R119",6.65k,R_0805,Res 6.65k 1% 0805 (ERR stage Ri lower half R118/119; C96/97 shunt the R116/R118 junction to GND so both are in the DC path - 10k here would give Av=-3.75 and put 2.500V out of null range)
2,RC0805FR-078K06L,Yageo,"AFE_Card R100,R101",8.06k,R_0805,Res 8.06k 1% 0805 (TIA Rf R100/101; sch says 8k -> 8.06k nearest E96)
2,RC0805FR-078K25L,Yageo,"AFE_Card R141,R143",8.25k,R_0805,Res 8.25k 1% 0805 (VB divider bottom; centres ERR on VREF_MID at DAC midscale)
